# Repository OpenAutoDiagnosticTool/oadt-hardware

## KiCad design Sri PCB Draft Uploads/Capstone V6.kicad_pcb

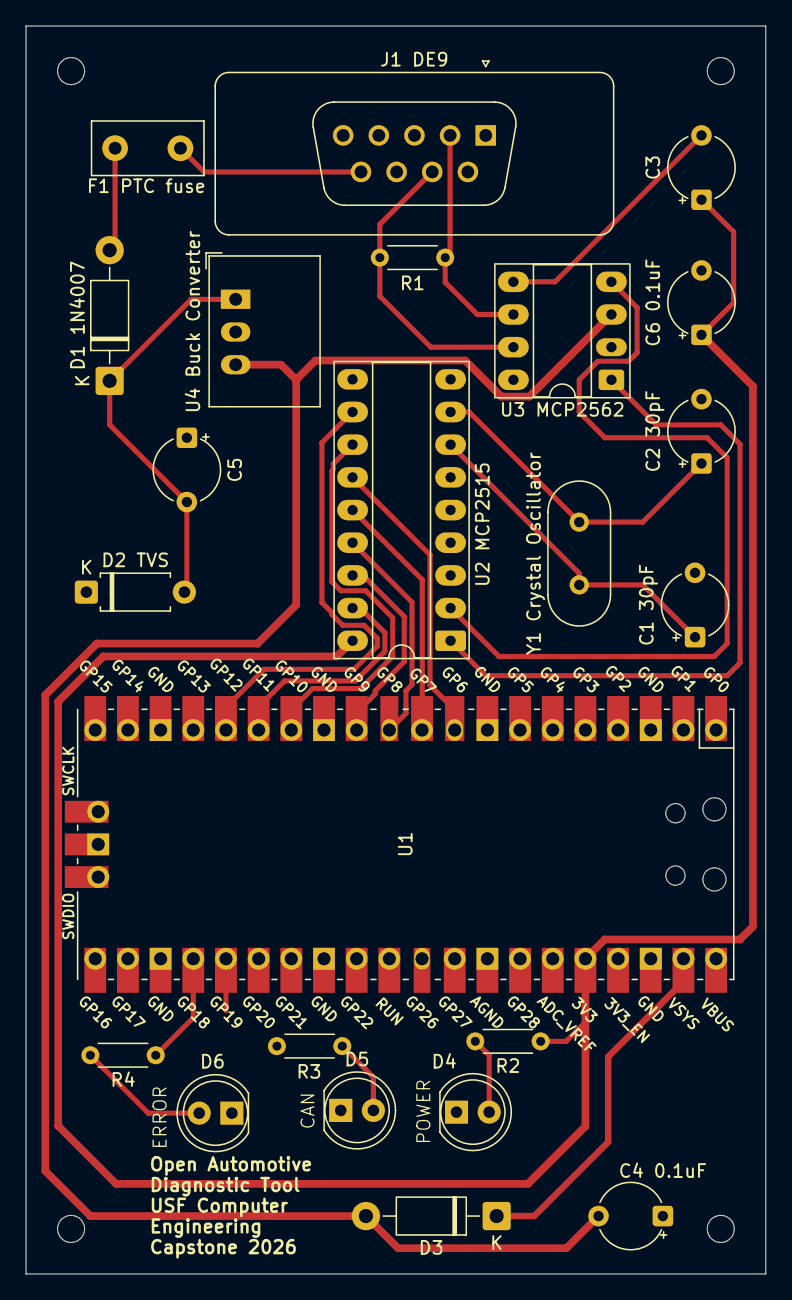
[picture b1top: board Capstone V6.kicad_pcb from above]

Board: 2 copper layers, 57.5 x 97.0 mm, 23 parts (0 on the bottom side), 26 nets.

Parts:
C1 30pF, C2 30pF: 30pF; CP_Radial_Tantal_D5.0mm_P5.00mm
C3, C4 0.1uF, C6 0.1uF: 0.1uF; CP_Radial_Tantal_D5.0mm_P5.00mm
C5: 100uF; CP_Radial_Tantal_D5.0mm_P5.00mm
D1 1N4007, D3: 1N4007; D_DO-41_SOD81_P10.16mm_Horizontal
D2 TVS: TVS; D_A-405_P7.62mm_Horizontal
D4, D5, D6: LED; LED_D5.0mm_IRBlack
F1 PTC fuse: PTC fuse; Fuse_Littelfuse_395Series
J1 DE9: DSUB-9_Socket_Vertical_P2.77x2.84mm
R1: 120 ohms (ONLY FOR BENCH TESTING); R_Axial_DIN0204_L3.6mm_D1.6mm_P5.08mm_Horizontal
R2, R3, R4: R; R_Axial_DIN0204_L3.6mm_D1.6mm_P5.08mm_Horizontal
U1: Pico; RPi_Pico_TH
U2 MCP2515: DIP-18_W7.62mm_Socket_LongPads
U3 MCP2562: DIP-8_W7.62mm_Socket_LongPads
U4 Buck Converter: Converter_DCDC_RECOM_R-78E-0.5_THT
Y1 Crystal Oscillator: Crystal; Crystal_HC49-4H_Vertical

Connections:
/3v3: C3.1, C6 0.1uF.1, R2.1, U1.36 (3V3), U2 MCP2515.18 (VDD)
/5v: C4 0.1uF.2, D3.2 (A), U3 MCP2562.3 (VDD), U4 Buck Converter.3 (5V)
/12v: F1 PTC fuse.1, J1 DE9.9 (12V)
/CAN: R3.1, U1.25 (GPIO19)
/CANH: J1 DE9.7 (CANH), R1.1, U3 MCP2562.7 (CANH)
/CANL: J1 DE9.2 (CANL), R1.2, U3 MCP2562.6 (CANL)
/GND: C1 30pF.2, C2 30pF.2, C4 0.1uF.1, C5.1, C6 0.1uF.2, D2 TVS.1 (K), D4.1 (K), D5.1 (K), D6.1 (K), J1 DE9.3 (GND), U1.3 (GND), U1.8 (GND), U1.13 (GND), U1.38 (GND), U2 MCP2515.9 (VSS_GND), U3 MCP2562.2 (VSS_GND), U3 MCP2562.8 (STBY), U4 Buck Converter.2 (GND)
/INTERRUPT: U1.14 (GPIO10), U2 MCP2515.12 (INT)
/RESET: U1.15 (GPIO11), U2 MCP2515.17 (RESET)
/RX0BF: U1.16 (GPIO12), U2 MCP2515.11 (RX0BF)
/RXCAN: U2 MCP2515.2 (RXCAN), U3 MCP2562.4 (RXD)
/SPI CLK: U1.9 (GPIO6), U2 MCP2515.13 (SCK)
/SPI CS: U1.12 (GPIO9), U2 MCP2515.16 (CS)
/SPI MISO: U1.11 (GPIO8), U2 MCP2515.15 (SO)
/SPI MOSI: U1.10 (GPIO7), U2 MCP2515.14 (SI)
/TXCAN: U2 MCP2515.1 (TXCAN), U3 MCP2562.1 (TXD)
/error: R4.1, U1.24 (GPIO18)
unnamed: D1 1N4007.2 (A), F1 PTC fuse.2
unnamed: C5.2, D1 1N4007.1 (K), D2 TVS.2 (A), U4 Buck Converter.1 (12V)
unnamed: D3.1 (K), U1.39 (VSYS)
unnamed: D4.2 (A), R2.2
unnamed: D5.2 (A), R3.2
unnamed: D6.2 (A), R4.2
unnamed: C2 30pF.1, U2 MCP2515.8 (OSC1), Y1 Crystal Oscillator.2
unnamed: C1 30pF.1, U2 MCP2515.7 (OSC2), Y1 Crystal Oscillator.1
unnamed: C3.2, U3 MCP2562.5 (VIO)

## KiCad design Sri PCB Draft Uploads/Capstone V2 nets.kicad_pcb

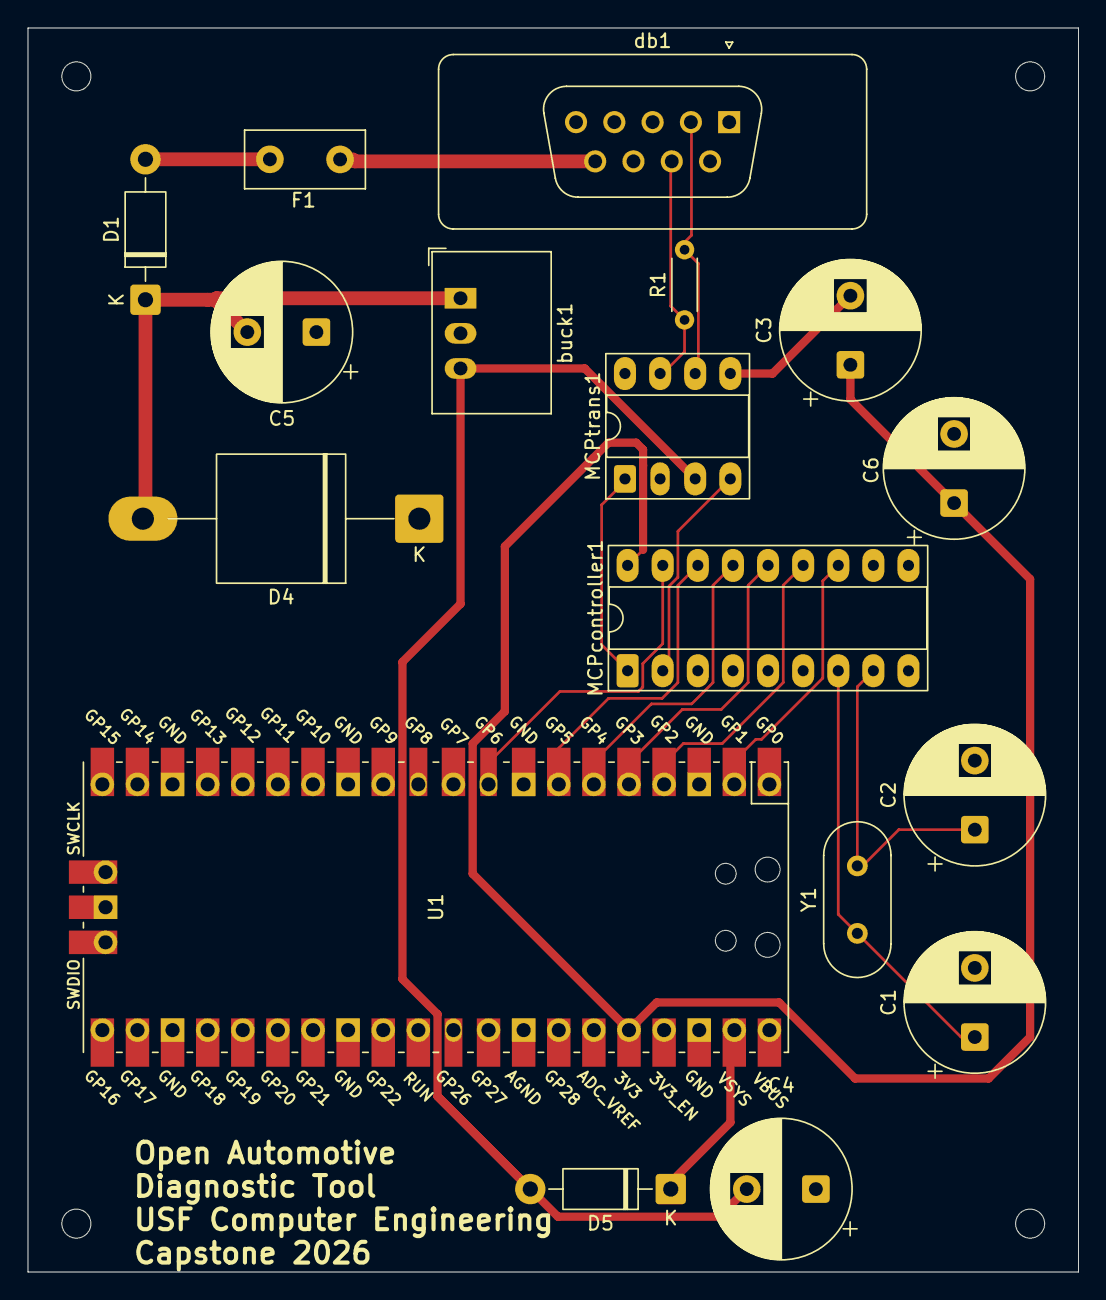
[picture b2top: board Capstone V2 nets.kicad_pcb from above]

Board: 2 copper layers, 76.0 x 90.0 mm, 17 parts (0 on the bottom side), 20 nets.

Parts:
C1: 30-33pF; CP_Radial_D10.0mm_P5.00mm
C2: 3-33pF; CP_Radial_D10.0mm_P5.00mm
C3, C4, C6: 0.1uF; CP_Radial_D10.0mm_P5.00mm
C5: 100uF; CP_Radial_D10.0mm_P5.00mm
D1, D5: 1N4007; D_DO-41_SOD81_P10.16mm_Horizontal
D4: TVS; D_P600_R-6_P20.00mm_Horizontal
F1: PTC fuse; Fuse_Littelfuse_395Series
MCPcontroller1: DIP-18_W7.62mm_Socket_LongPads
MCPtrans1: DIP-8_W7.62mm_Socket_LongPads
R1: 120 ohms (ONLY FOR BENCH TESTING); R_Axial_DIN0204_L3.6mm_D1.6mm_P5.08mm_Horizontal
U1: Pico; RPi_Pico_TH
Y1: Crystal; Crystal_HC49-4H_Vertical
buck1: Converter_DCDC_RECOM_R-78E-0.5_THT
db1: DSUB-9_Socket_Vertical_P2.77x2.84mm

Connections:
/3v3: C3.1, C6.1, MCPcontroller1.18 (VDD), U1.36 (3V3)
/5v: C4.2, D5.2 (A), MCPtrans1.3 (VDD), buck1.3 (5V)
/12v: F1.1, db1.9 (12V)
/CANH: MCPtrans1.7 (CANH), R1.1, db1.7 (CANH)
/CANL: MCPtrans1.6 (CANL), R1.2, db1.2 (CANL)
/GND: C1.2, C2.2, C4.1, C5.1, C6.2, D4.1 (K), MCPcontroller1.9 (VSS_GND), MCPtrans1.2 (VSS_GND), MCPtrans1.8 (STBY), U1.3 (GND), U1.8 (GND), U1.13 (GND), U1.38 (GND), buck1.2 (GND), db1.3 (GND)
/INTERRUPT: MCPcontroller1.12 (INT), U1.2 (GPIO1)
/RESET: MCPcontroller1.17 (RESET), U1.9 (GPIO6)
/RXCAN: MCPcontroller1.2 (RXCAN), MCPtrans1.4 (RXD)
/SPI CLK: MCPcontroller1.13 (SCK), U1.4 (GPIO2)
/SPI CS: MCPcontroller1.16 (CS), U1.7 (GPIO5)
/SPI MISO: MCPcontroller1.15 (SO), U1.6 (GPIO4)
/SPI MOSI: MCPcontroller1.14 (SI), U1.5 (GPIO3)
/TXCAN: MCPcontroller1.1 (TXCAN), MCPtrans1.1 (TXD)
unnamed: D1.2 (A), F1.2
unnamed: C5.2, D1.1 (K), D4.2 (A), buck1.1 (12V)
unnamed: D5.1 (K), U1.39 (VSYS)
unnamed: C2.1, MCPcontroller1.8 (OSC1), Y1.2
unnamed: C1.1, MCPcontroller1.7 (OSC2), Y1.1
unnamed: C3.2, MCPtrans1.5 (VIO)

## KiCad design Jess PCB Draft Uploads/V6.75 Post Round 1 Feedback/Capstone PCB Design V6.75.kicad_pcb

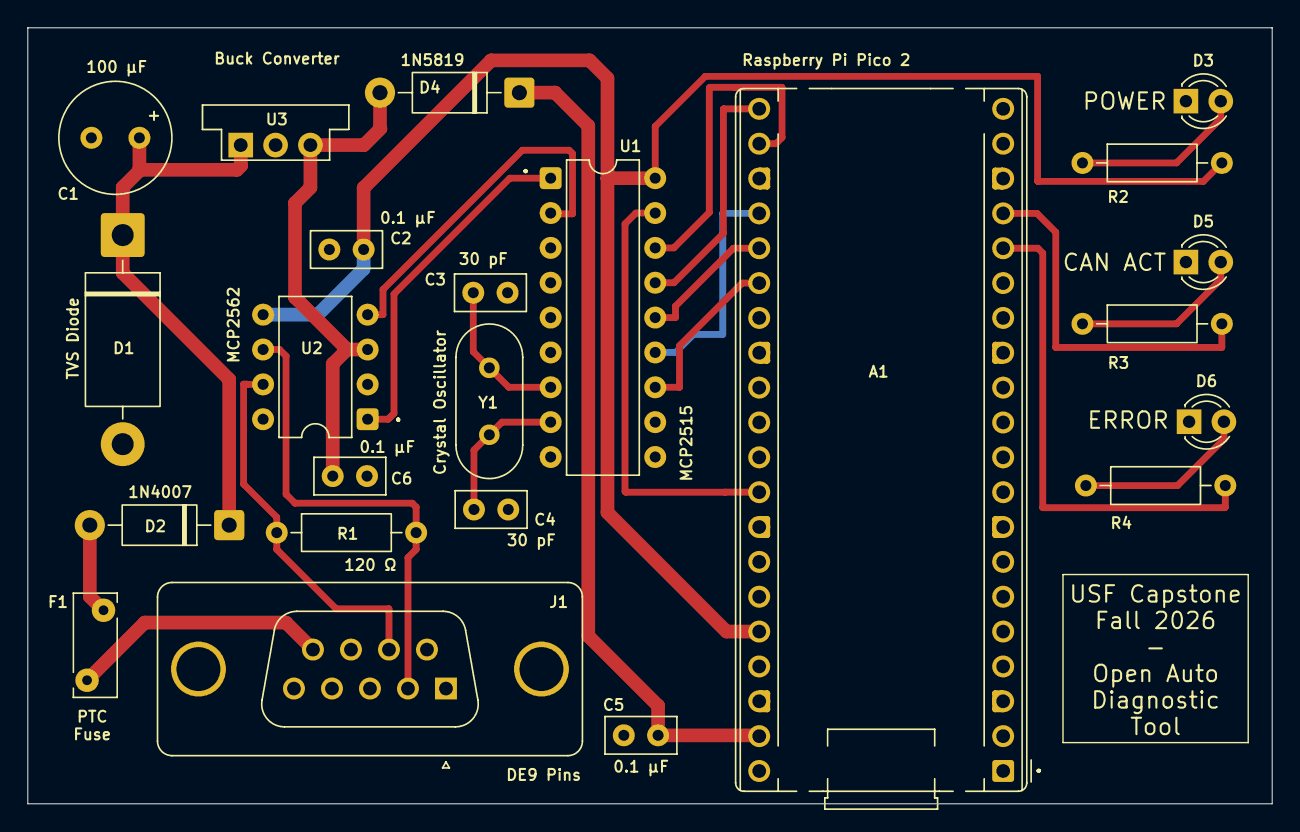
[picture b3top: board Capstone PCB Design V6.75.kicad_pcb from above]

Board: 2 copper layers, 90.7 x 56.6 mm, 27 parts (0 on the bottom side), 24 nets.

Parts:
A1: RaspberryPi_Pico; RaspberryPi_Pico_Common_THT
C1: C_Polarized_US; C_Radial_D8.0mm_H11.5mm_P3.50mm
C2, C5, C6: 0.1 µF; C_Disc_D5.0mm_W2.5mm_P2.50mm
C3, C4: 30 pF; C_Disc_D5.0mm_W2.5mm_P2.50mm
D1: TVS Diode; D_DO-201AD_P15.24mm_Horizontal
D2: 1N4007; D_DO-41_SOD81_P10.16mm_Horizontal
D3, D5, D6: LED; LED_D3.0mm
D4: 1N5819; D_DO-41_SOD81_P10.16mm_Horizontal
F1: PTC Fuse; Fuse_Bourns_MF-RHT050
H1, H2, H3, H4: MountingHole; MountingHole_4.3mm_M4
J1: DE9_Pins_MountingHoles; DSUB-9_Pins_Vertical_P2.77x2.84mm_MountingHoles
R1, R2, R3, R4: 120 Ohm Resistor; R_Axial_DIN0207_L6.3mm_D2.5mm_P10.16mm_Horizontal
U1: MCP2515-xSO; DIP-18_W7.62mm
U2: MCP2562-E-P; DIP-8_W7.62mm
U3: Buck Converter; Converter_DCDC_Murata_OKI-78SR_Vertical
Y1: Crystal Oscillator; Crystal_HC49-4H_Vertical

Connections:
+3.3V: A1.36 (3V3), C2.1, R2.2, U1.18 (VDD), U2.5 (Vio)
+5V: C6.2, D4.2 (A), U2.3 (VDD), U3.3 (5V)
+12V: F1.2, J1.9 (12V)
CAN Act: A1.17 (GPIO13), R3.2
CANH: J1.7 (CANH), R1.1, U2.7 (CANH)
CANL: J1.2 (CANL), R1.2, U2.6 (CANL)
CS: A1.22 (GPIO17), U1.16 (~CS)
Error: A1.16 (GPIO12), R4.2
GND: A1.3 (GND), A1.8 (GND), A1.13 (GND), A1.18 (GND), A1.23 (GND), A1.28 (GND), A1.38 (GND), C1.2, C2.2, C3.2, C4.2, C5.1, C6.1, D1.2 (A), D3.1 (K), D5.1 (K), D6.1 (K), J1.3 (GND), U1.9 (VSS), U2.2 (VSS), U2.8 (STBY), U3.2 (GND)
INT: A1.26 (GPIO20), U1.12 (~INT)
unnamed: A1.39 (VSYS), C5.2, D4.1 (K)
unnamed: C1.1, D1.1 (K), D2.1 (K), U3.1 (12V)
unnamed: D2.2 (A), F1.1
unnamed: D3.2 (A), R2.1
unnamed: D5.2 (A), R3.1
unnamed: D6.2 (A), R4.1
unnamed: C4.1, U1.8 (OSC1), Y1.2
unnamed: C3.1, U1.7 (OSC2), Y1.1
RST: A1.32 (GPIO27_ADC1), U1.17 (~RESET)
RX: U1.2 (RXCAN), U2.4 (RXD)
SCK: A1.24 (GPIO18), U1.13 (SCK)
SI: A1.25 (GPIO19), U1.14 (SI)
SO: A1.21 (GPIO16), U1.15 (SO)
TX: U1.1 (TXCAN), U2.1 (TXD)
